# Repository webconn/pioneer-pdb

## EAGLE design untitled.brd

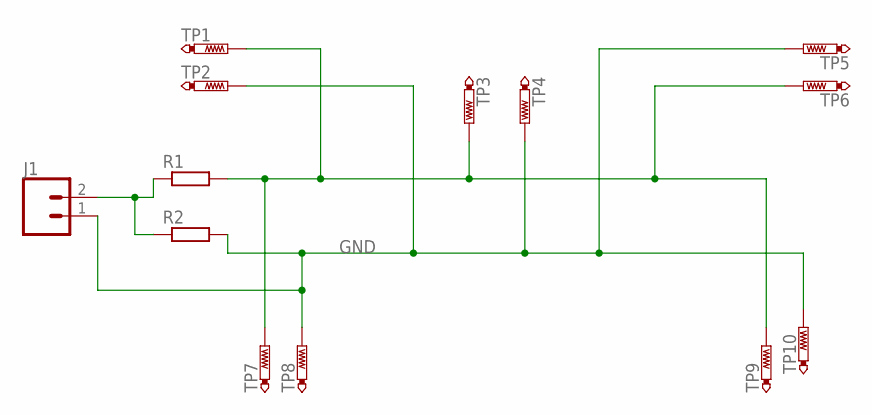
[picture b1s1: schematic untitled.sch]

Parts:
J1: CONN_02LOCK_LONGPADS; 1X02_LOCK_LONGPADS
R1, R2: R-EU_0207/12; 0207/12
TP1, TP2, TP3, TP4, TP5, TP6, TP7, TP8, TP9, TP10: PTR1TP20R; TP20R

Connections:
GND: J1.1, R2.2, TP2.TP, TP4.TP, TP5.TP, TP8.TP, TP10.TP
unnamed: J1.2, R1.1, R2.1
VCC: R1.2, TP1.TP, TP3.TP, TP6.TP, TP7.TP, TP9.TP

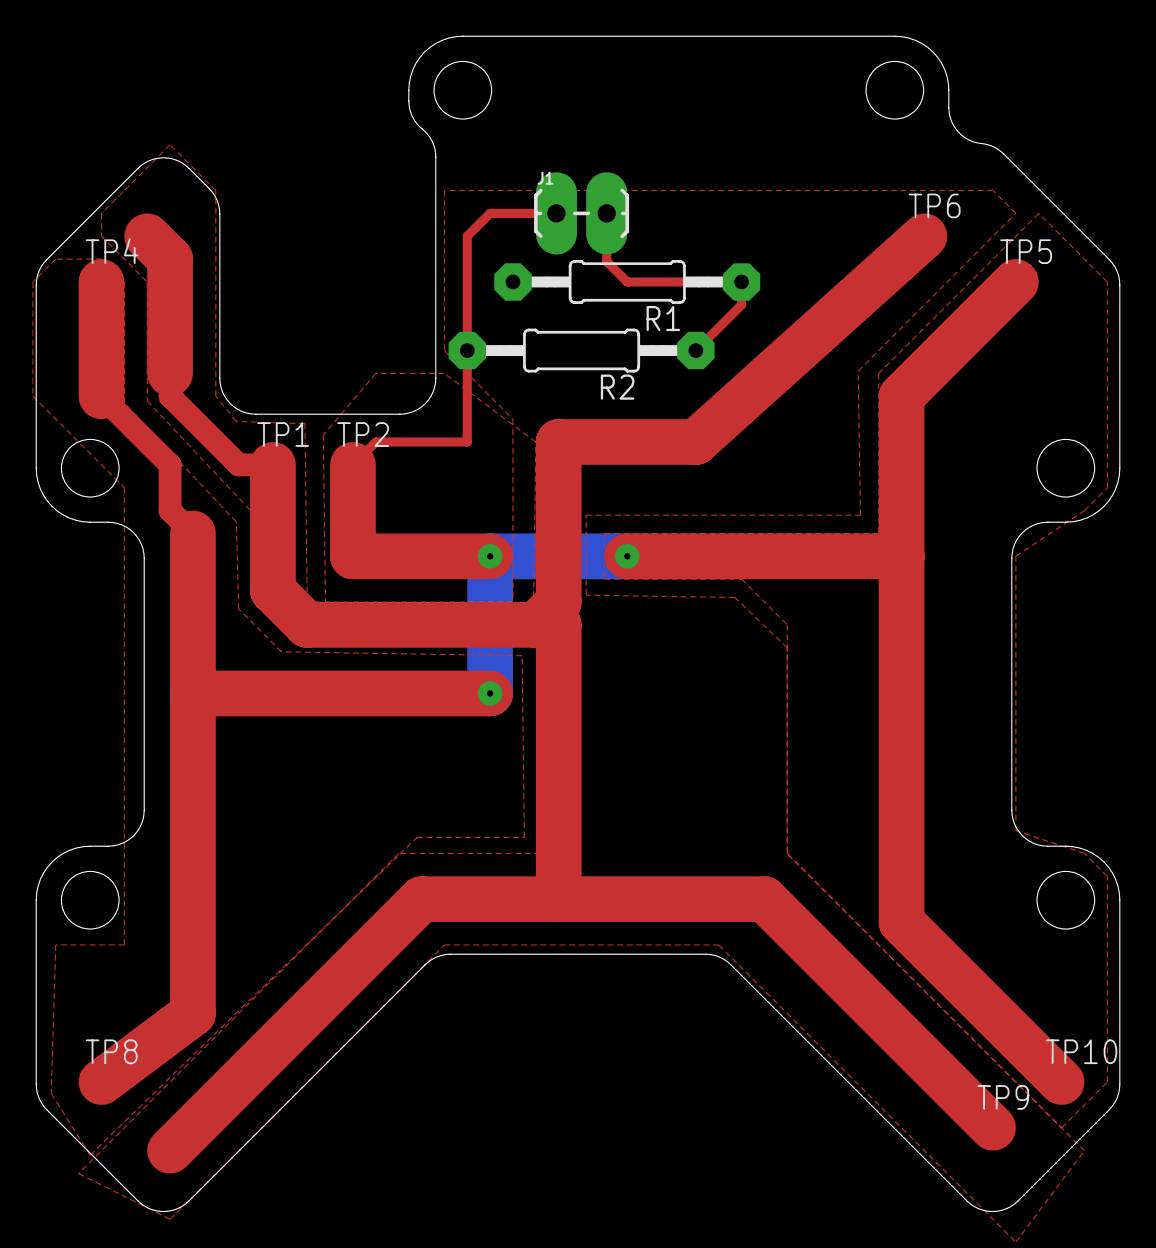
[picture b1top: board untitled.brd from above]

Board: 2 copper layers, 60.2 x 65.3 mm, 13 parts (0 on the bottom side), 3 nets.

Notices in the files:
parts and their libraries:
SparkFun-Connectors: Licensing: Creative Commons ShareAlike 4.0 International - https://creativecommons.org/licenses/by-sa/4.0
